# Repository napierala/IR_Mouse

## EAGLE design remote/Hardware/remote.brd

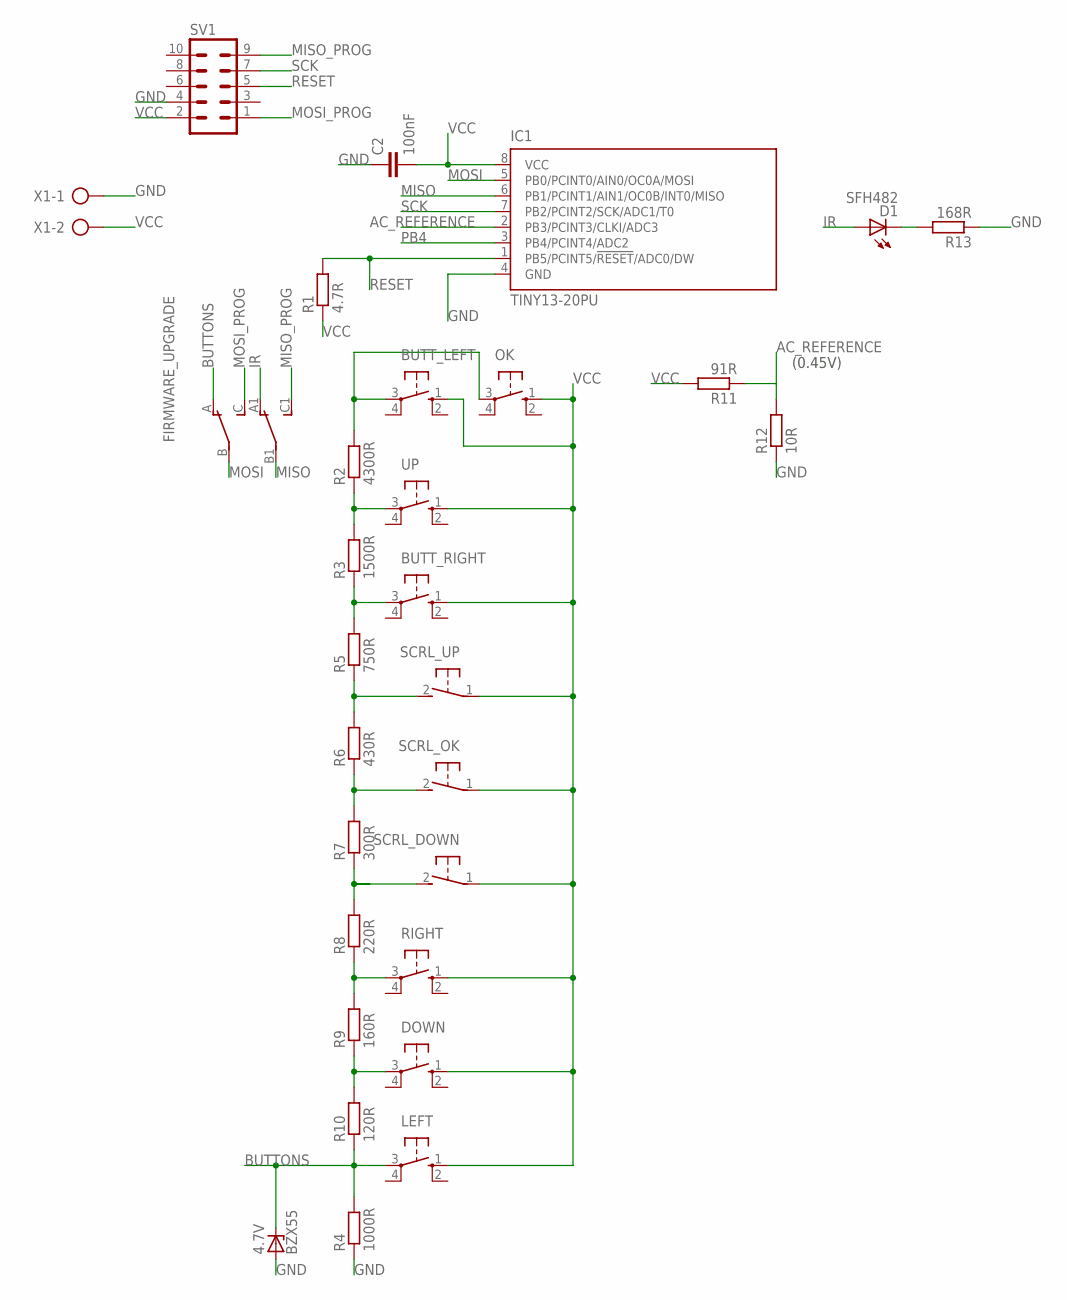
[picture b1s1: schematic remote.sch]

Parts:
4.7V: BZX55; DO35Z10
BUTT_LEFT: 10-XX; B3F-10XX
BUTT_RIGHT: 10-XX; B3F-10XX; MPN B3F-1000
C2: 100nF; C050-024X044
D1: SFH482
DOWN: 10-XX; B3F-10XX; MPN B3F-1000
FIRMWARE_UPGRADE: MINI_SLIDING_SWITCHS; MINI_SLIDING_SWITCH
IC1: TINY13-20PU; DIL08
LEFT: 10-XX; B3F-10XX
OK: 10-XX; B3F-10XX; MPN B3F-1000
R1: 4.7R; 0204/7
R2: 4300R; 0204/7
R3: 1500R; 0204/7
R4: 1000R; 0204/7
R5: 750R; 0204/7
R6: 430R; 0204/7
R7: 300R; 0204/7
R8: 220R; 0204/7
R9: 160R; 0204/7
R10: 120R; 0204/7
R11: 91R; 0204/7
R12: 10R; 0204/7
R13: 168R; 0204/7
RIGHT: 10-XX; B3F-10XX; MPN B3F-1000
SCRL_DOWN: 31-XX; B3F-31XX; MPN B3F-3100
SCRL_OK: 31-XX; B3F-31XX; MPN B3F-3100
SCRL_UP: 31-XX; B3F-31XX
SV1: ML10L
UP: 10-XX; B3F-10XX; MPN B3F-1000
X1: AK300/2

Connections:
AC_REFERENCE: IC1.2 (PB3/PCINT3/CLKI/ADC3), R11.1, R12.2
BUTTONS: 4.7V.C, FIRMWARE_UPGRADE.A, LEFT.3, R4.2, R10.1
GND: 4.7V.A, C2.1, IC1.4 (GND), R4.1, R12.1, R13.1, SV1.4, X1.1
IR: D1.A, FIRMWARE_UPGRADE.A1
MISO: FIRMWARE_UPGRADE.B1, IC1.6 (PB1/PCINT1/AIN1/OC0B/INT0/MISO)
MISO_PROG: FIRMWARE_UPGRADE.C1, SV1.9
MOSI: FIRMWARE_UPGRADE.B, IC1.5 (PB0/PCINT0/AIN0/OC0A/MOSI)
MOSI_PROG: FIRMWARE_UPGRADE.C, SV1.1
unnamed: R2.1, R3.2, UP.3
unnamed: BUTT_LEFT.3, OK.3, R2.2
unnamed: R6.1, R7.2, SCRL_OK.2 (S)
unnamed: R7.1, R8.2, SCRL_DOWN.2 (S)
unnamed: R8.1, R9.2, RIGHT.3
unnamed: DOWN.3, R9.1, R10.2
unnamed: D1.K (C), R13.2
unnamed: R5.1, R6.2, SCRL_UP.2 (S)
unnamed: BUTT_RIGHT.3, R3.1, R5.2
PB4: IC1.3 (PB4/PCINT4/ADC2)
RESET: IC1.1 (PB5/PCINT5/!RESET!/ADC0/DW), R1.2, SV1.5
SCK: IC1.7 (PB2/PCINT2/SCK/ADC1/T0), SV1.7
VCC: BUTT_LEFT.1 (S), BUTT_RIGHT.1 (S), C2.2, DOWN.1 (S), IC1.8 (VCC), LEFT.1 (S), OK.1 (S), R1.1, R11.2, RIGHT.1 (S), SCRL_DOWN.1, SCRL_OK.1, SCRL_UP.1, SV1.2, UP.1 (S), X1.2

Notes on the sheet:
(0.45V)

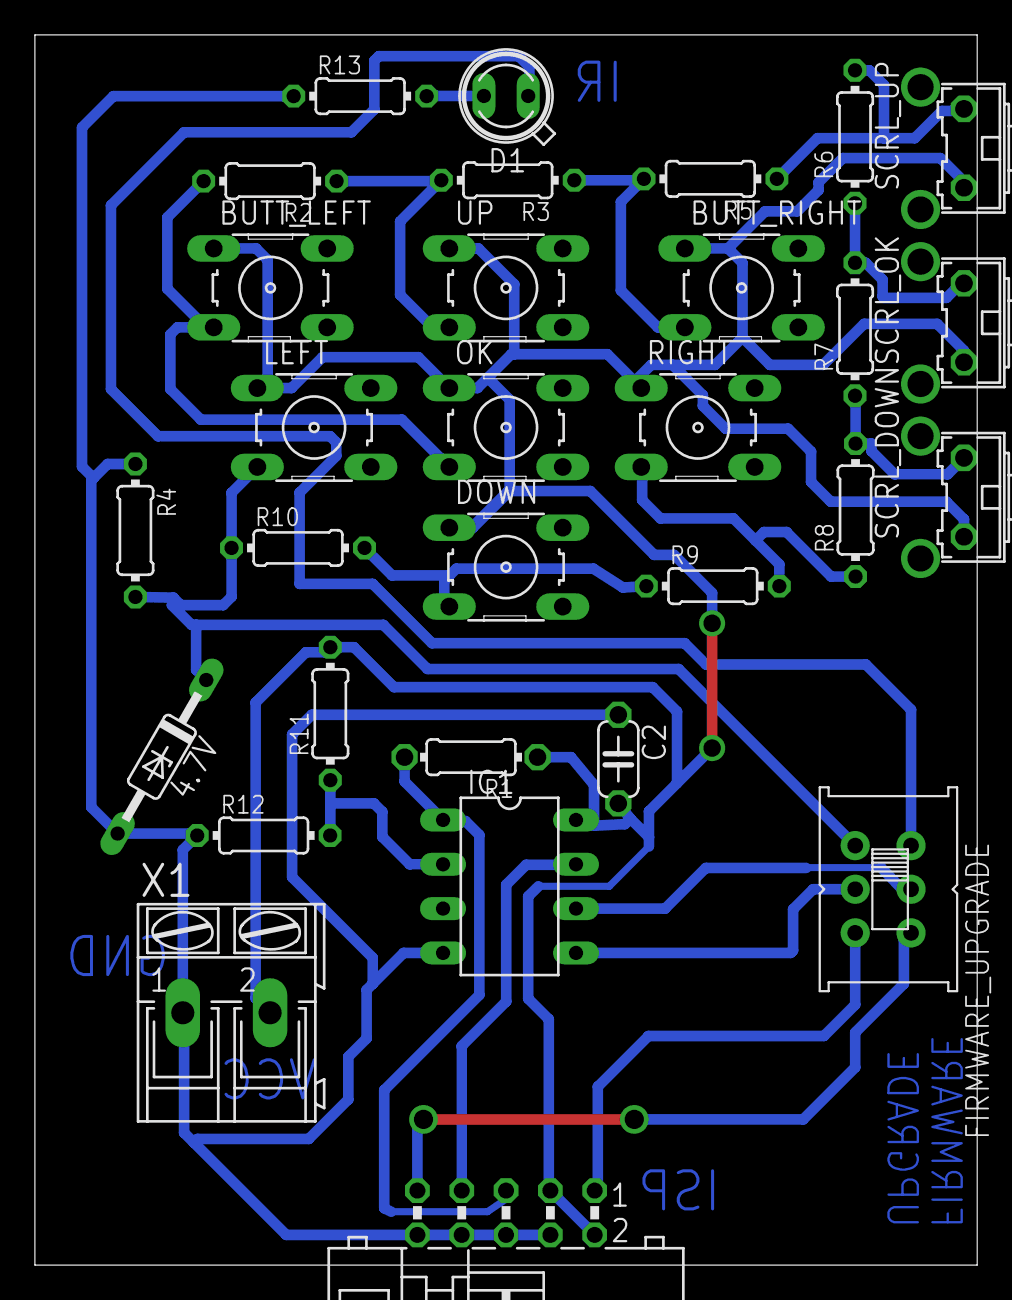
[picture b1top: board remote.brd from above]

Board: 2 copper layers, 54.0 x 70.5 mm, 30 parts (0 on the bottom side), 20 nets.

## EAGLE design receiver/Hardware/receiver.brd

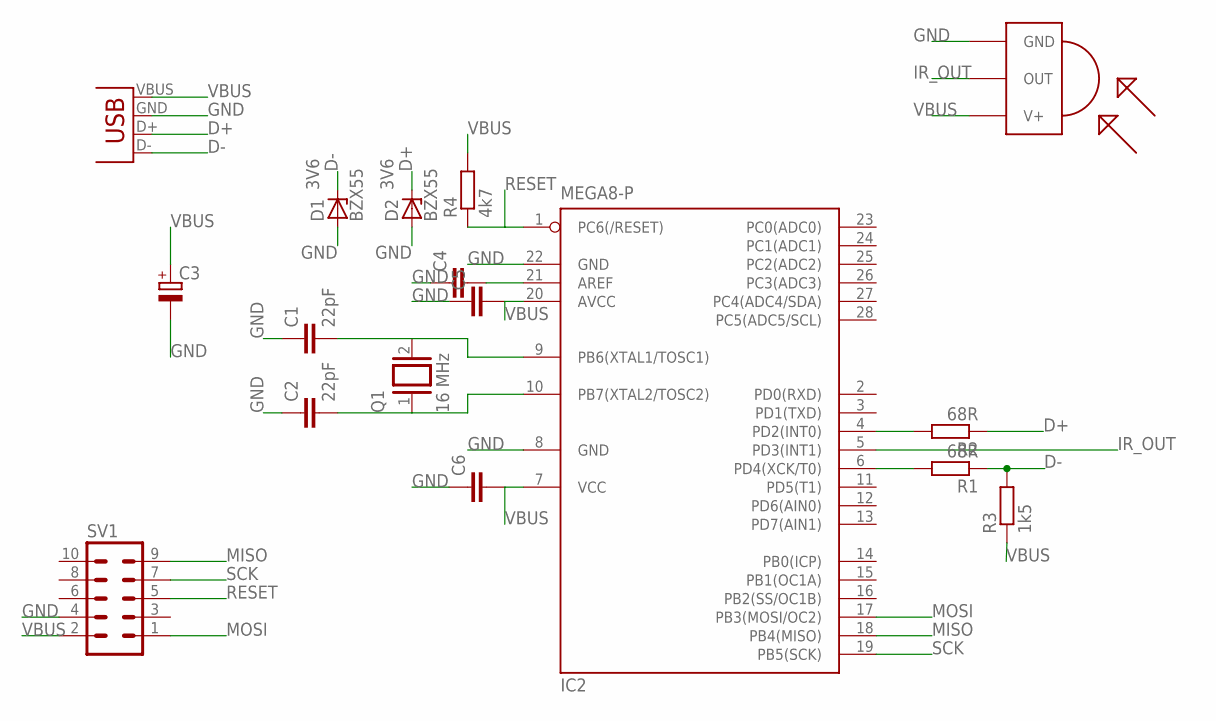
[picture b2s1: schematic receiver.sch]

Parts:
C1, C2: 22pF; C050-025X075
C3: CPOL-EUE2-5; E2-5
C4, C5, C6: C-EU050-024X044; C050-024X044
D1, D2: BZX55; DO35Z10
IC2: MEGA8-P; DIL28-3
JP1: USB-A-H
Q1: 16 MHz; QS
R1, R2: 68R; 0204/7
R3: 1k5; 0204/7
R4: 4k7; 0204/7
SV1: ML10L
TSOP1: TSOP1730; TSOP17XX

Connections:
COS: C2.2, IC2.10 (PB7(XTAL2/TOSC2)), Q1.1
D+: D2.C, JP1.D+ (D-), R2.1
D-: D1.C, JP1.D- (D+), R1.1, R3.2
GND: C1.1, C2.1, C3.-, C4.1, C5.1, C6.1, D1.A, D2.A, IC2.8 (GND), IC2.22 (GND), JP1.GND (VBUS), SV1.4, TSOP1.GND
IR_OUT: IC2.5 (PD3(INT1)), TSOP1.OUT
MISO: IC2.18 (PB4(MISO)), SV1.9
MOSI: IC2.17 (PB3(MOSI/OC2)), SV1.1
unnamed: C4.2, IC2.21 (AREF)
unnamed: C1.2, IC2.9 (PB6(XTAL1/TOSC1)), Q1.2
unnamed: IC2.6 (PD4(XCK/T0)), R1.2
unnamed: IC2.4 (PD2(INT0)), R2.2
RESET: IC2.1 (PC6(/RESET)), R4.1, SV1.5
SCK: IC2.19 (PB5(SCK)), SV1.7
VBUS: C3.+, C5.2, C6.2, IC2.7 (VCC), IC2.20 (AVCC), JP1.VBUS (GND), R3.1, R4.2, SV1.2, TSOP1.V+

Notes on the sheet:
3V6

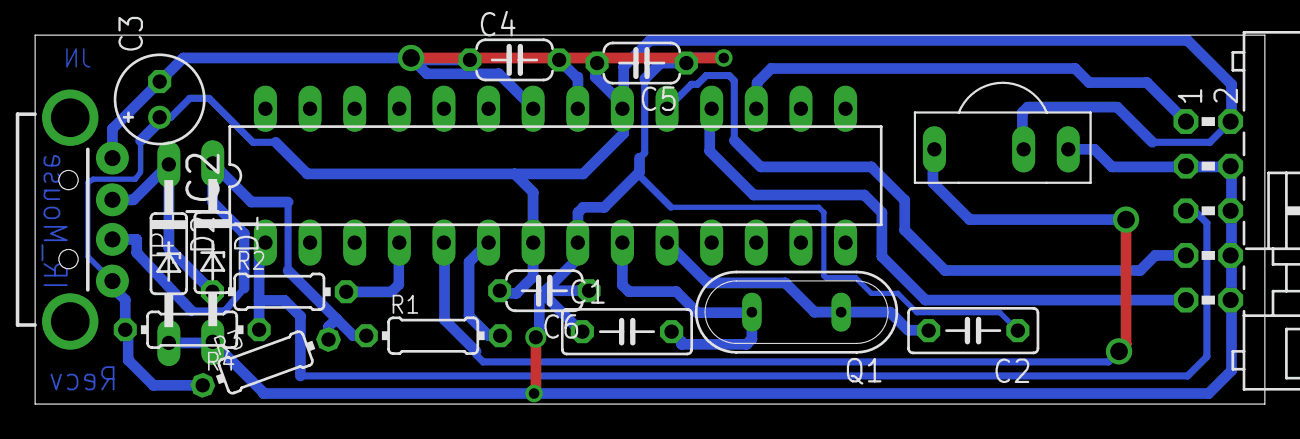
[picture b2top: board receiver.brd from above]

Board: 2 copper layers, 70.0 x 21.0 mm, 17 parts (0 on the bottom side), 14 nets.

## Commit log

2013-06-01 git init
2013-06-01 Struktura plikow
2013-06-01 Plytka USB odbiornika
2013-06-07 Naprawa schematu
2013-06-07 Schemat Pilota
2013-06-07 Działający soft dla odbiornika, rusza myszke po ekranie sam, nie testowany odbiornik podczerwieni, który jest zaimplementowany jako funkcja(a nie przerwanie)
2013-06-08 Naprawa Plytki pilota, gotowe do termotransferu
2013-06-11 Działający Pilot

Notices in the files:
parts and their libraries:
SparkFun-Connectors: Licensing: CC v3.0 Share-Alike You are welcome to use this library for commercial purposes.
